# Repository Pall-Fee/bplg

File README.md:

BPLG is an attempt at a delightfully exessive *wireless haptic feedback device.*

The Goals for this device is to create a wireless vibrational butt plug that is
- open source
- cost effective & accessible
- supports [buttplug.io](https://buttplug.io/) 
- comfortable
- **safe!**

We also aim to achieve a device that is
- easy to assemble
- long running
- powerful
- versatile
- responsive
 
Design of the butt plug is broken down to:
- KiCad Files (PCBA)
- Freecad Files (TOPA)

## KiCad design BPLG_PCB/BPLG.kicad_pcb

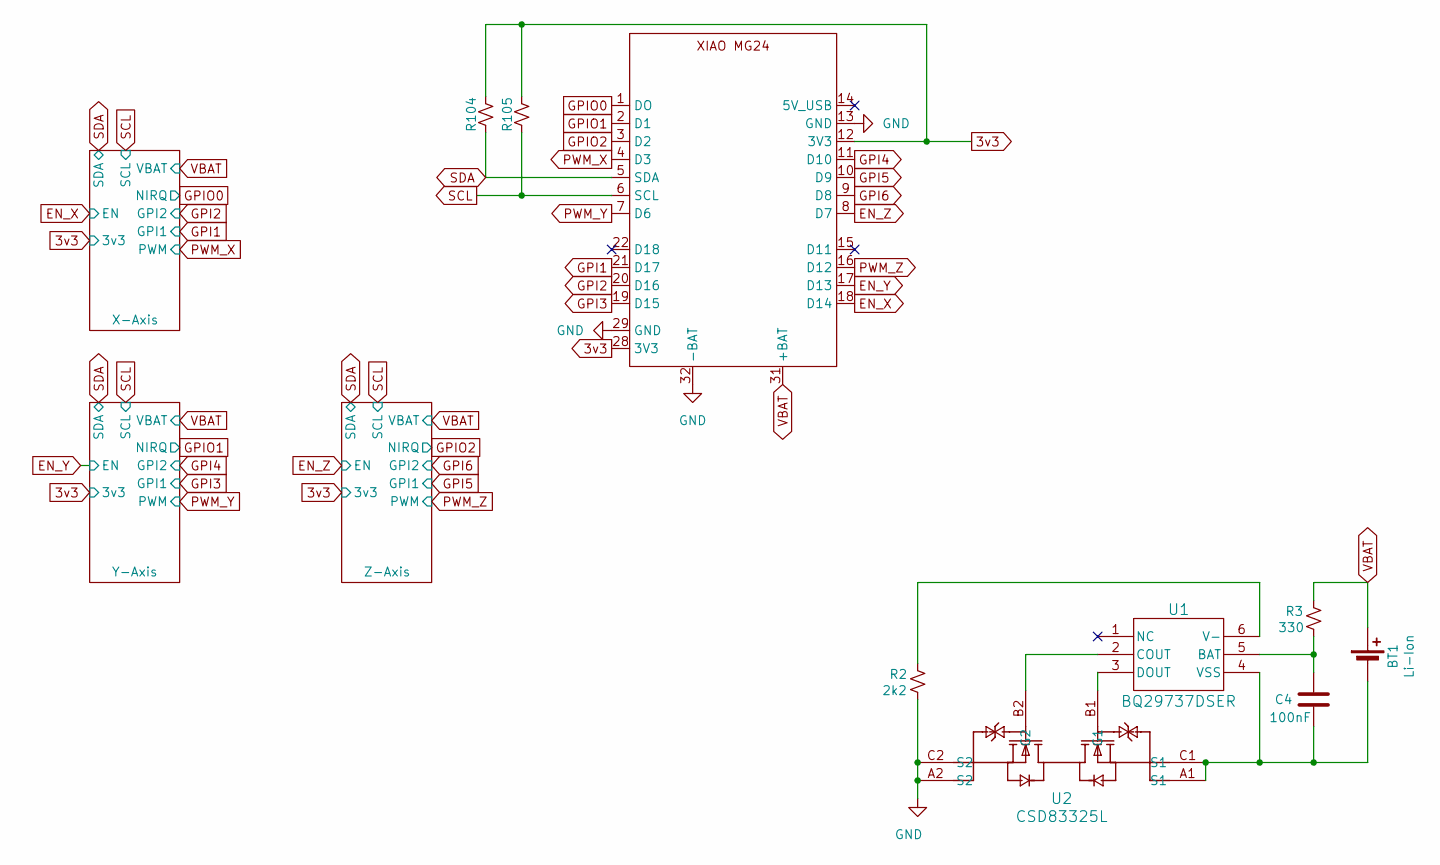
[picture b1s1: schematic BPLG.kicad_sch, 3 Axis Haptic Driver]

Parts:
BT1: Li-Ion; Battery Leads
C4: 100nF; C_0805_2012Metric
R2, R104, R105: 2k2; R_0402_1005Metric
R3: 330; R_0402_1005Metric
U1: BQ29737DSER; DSE0006A
U2: CSD83325L; YJE0006A
XIAO1: XIAO-MG24-SMD

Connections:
3v3: R104.1, R105.1, XIAO1.12 (3V3), XIAO1.28 (3V3); also elsewhere on the board
EN_X: XIAO1.18 (D14); also elsewhere on the board
EN_Y: XIAO1.17 (D13); also elsewhere on the board
EN_Z: XIAO1.8 (D7); also elsewhere on the board
GND: R2.2, U2.A2 (S2), U2.C2 (S2), XIAO1.13 (GND), XIAO1.29 (GND), XIAO1.32 (-BAT); also elsewhere on the board
GPI1: XIAO1.21 (D17); also elsewhere on the board
GPI2: XIAO1.20 (D16); also elsewhere on the board
GPI3: XIAO1.19 (D15); also elsewhere on the board
GPI4: XIAO1.11 (D10); also elsewhere on the board
GPI5: XIAO1.10 (D9); also elsewhere on the board
GPI6: XIAO1.9 (D8); also elsewhere on the board
GPIO0: XIAO1.1 (DO); also elsewhere on the board
GPIO1: XIAO1.2 (D1); also elsewhere on the board
GPIO2: XIAO1.3 (D2); also elsewhere on the board
unnamed: BT1.2 (-), C4.2, U1.4 (VSS), U2.A1 (S1), U2.C1 (S1)
unnamed: C4.1, R3.2, U1.5 (BAT)
unnamed: U1.2 (COUT), U2.B2 (G2)
unnamed: U1.3 (DOUT), U2.B1 (G1)
unnamed: R2.1, U1.6 (V-)
PWM_X: XIAO1.4 (D3); also elsewhere on the board
PWM_Y: XIAO1.7 (D6); also elsewhere on the board
PWM_Z: XIAO1.16 (D12); also elsewhere on the board
SCL: R105.2, XIAO1.6 (SCL); also elsewhere on the board
SDA: R104.2, XIAO1.5 (SDA); also elsewhere on the board
VBAT: BT1.1 (+), R3.1, XIAO1.31 (+BAT); also elsewhere on the board

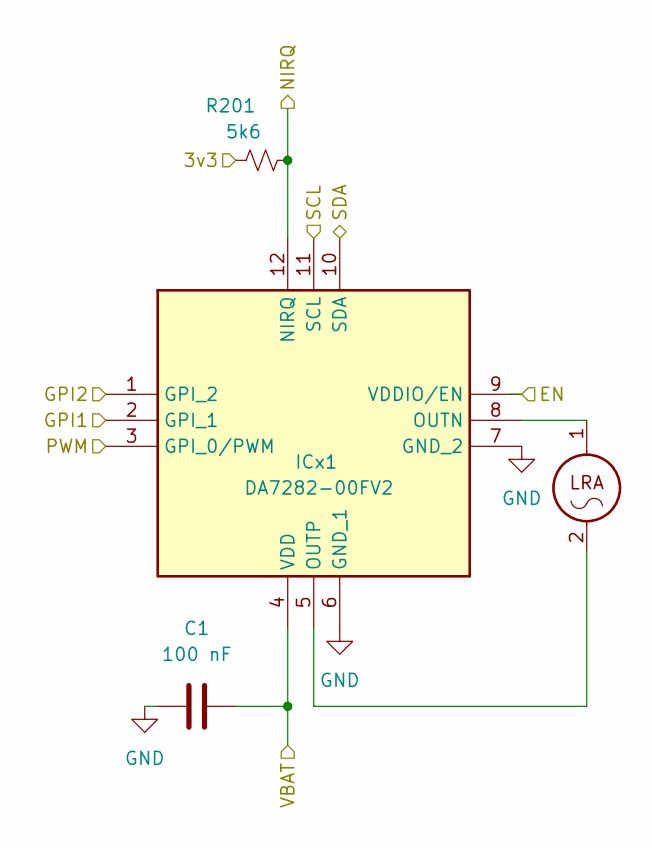
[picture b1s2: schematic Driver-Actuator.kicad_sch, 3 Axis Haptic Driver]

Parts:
C1: 100 nF; C_0805_2012Metric
ICx1: DA7282-00FV2; QFN65P300X300X84-12N-D; Manufacturer_Part_Number DA7282-00FV2; Mouser Part Number 724-DA7282-00FV2
Mx1: VLV221007E
R201: 5k6; R_0402_1005Metric

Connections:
3v3: R201.1; also elsewhere on the board
EN_X: ICx1.9 (VDDIO/EN); also elsewhere on the board
GND: C1.2, ICx1.6 (GND_1), ICx1.7 (GND_2); also elsewhere on the board
GPI1: ICx1.2 (GPI_1); also elsewhere on the board
GPI2: ICx1.1 (GPI_2); also elsewhere on the board
GPIO0: ICx1.12 (NIRQ), R201.2; also elsewhere on the board
unnamed: ICx1.8 (OUTN), Mx1.1
unnamed: ICx1.5 (OUTP), Mx1.2
PWM_X: ICx1.3 (GPI_0/PWM); also elsewhere on the board
SCL: ICx1.11 (SCL); also elsewhere on the board
SDA: ICx1.10 (SDA); also elsewhere on the board
VBAT: C1.1, ICx1.4 (VDD); also elsewhere on the board

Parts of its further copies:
C2, C3: 100 nF; C_0805_2012Metric
ICy1: DA7282-00FV2; QFN65P300X300X84-12N-D; Manufacturer_Part_Number DA7282-00FV2; Mouser Part Number 724-DA7282-00FV2
ICz1: DA7282-00FV2; QFN65P300X300X84-12N-D; Manufacturer_Part_Number DA7282-00FV2; Mouser Part Number 724-DA7282-00FV2
My1: VLV221007E
Mz1: VLV221007E
R202, R203: 5k6; R_0402_1005Metric

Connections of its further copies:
3v3: R202.1, R203.1; also elsewhere on the board
EN_Y: ICy1.9 (VDDIO/EN); also elsewhere on the board
EN_Z: ICz1.9 (VDDIO/EN); also elsewhere on the board
GND: C2.2, C3.2, ICy1.6 (GND_1), ICy1.7 (GND_2), ICz1.6 (GND_1), ICz1.7 (GND_2); also elsewhere on the board
GPI3: ICy1.2 (GPI_1); also elsewhere on the board
GPI4: ICy1.1 (GPI_2); also elsewhere on the board
GPI5: ICz1.2 (GPI_1); also elsewhere on the board
GPI6: ICz1.1 (GPI_2); also elsewhere on the board
GPIO1: ICy1.12 (NIRQ), R202.2; also elsewhere on the board
GPIO2: ICz1.12 (NIRQ), R203.2; also elsewhere on the board
unnamed: ICy1.8 (OUTN), My1.1
unnamed: ICy1.5 (OUTP), My1.2
unnamed: ICz1.8 (OUTN), Mz1.1
unnamed: ICz1.5 (OUTP), Mz1.2
PWM_Y: ICy1.3 (GPI_0/PWM); also elsewhere on the board
PWM_Z: ICz1.3 (GPI_0/PWM); also elsewhere on the board
SCL: ICy1.11 (SCL), ICz1.11 (SCL); also elsewhere on the board
SDA: ICy1.10 (SDA), ICz1.10 (SDA); also elsewhere on the board
VBAT: C2.1, C3.1, ICy1.4 (VDD), ICz1.4 (VDD); also elsewhere on the board

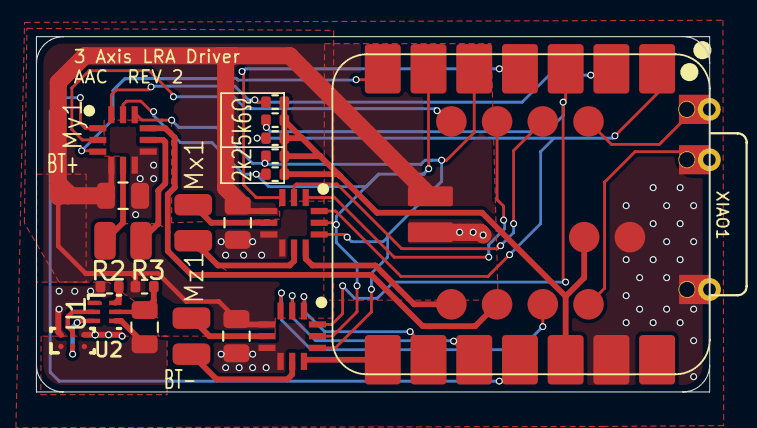
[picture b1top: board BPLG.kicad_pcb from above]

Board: 2 copper layers, 37.4 x 19.8 mm, 23 parts (0 on the bottom side), 31 nets.

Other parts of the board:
D11, D18: Castleted Pin; Castelated Pin
GND: Castleted Pin; Castelated Pin

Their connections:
GND: GND.1; also elsewhere on the board

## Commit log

2025-06-03 Initial Release
2025-06-14 Correct README.md
